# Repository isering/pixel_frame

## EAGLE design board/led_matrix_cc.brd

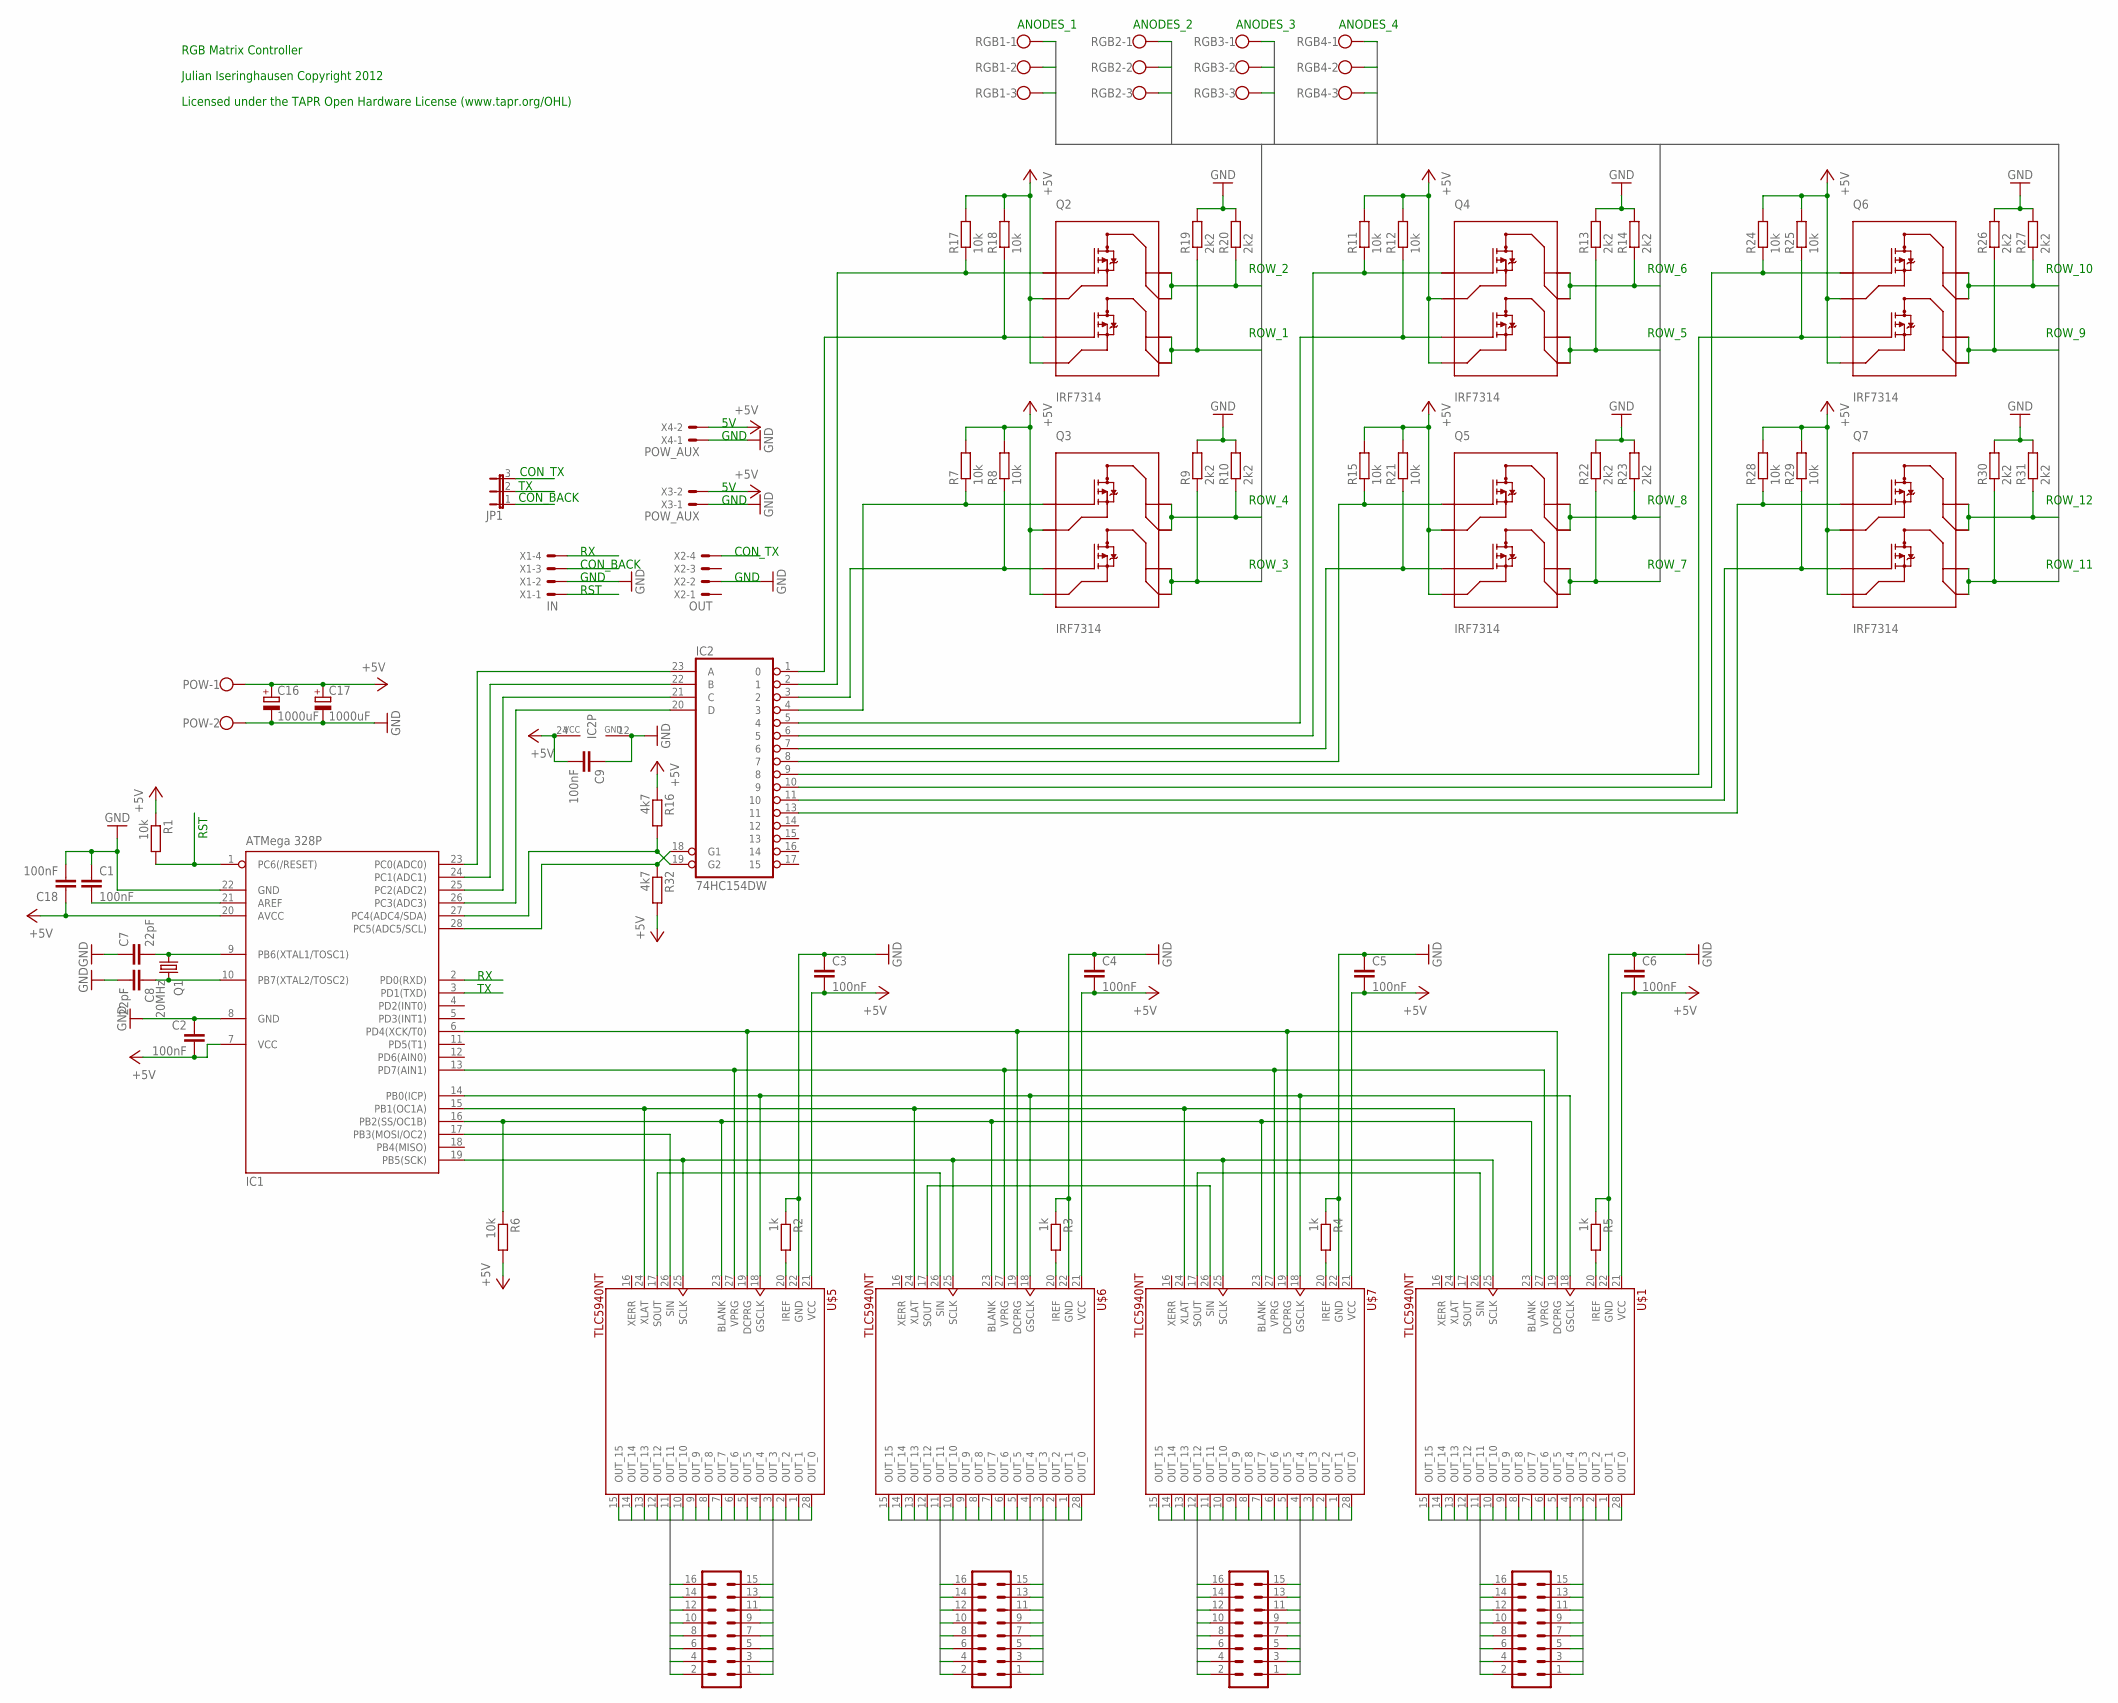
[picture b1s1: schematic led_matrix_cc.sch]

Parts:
C1, C2, C3, C4, C5, C6, C9, C18: 100nF; C1206
C7, C8: 22pF; C1206
C16, C17: 1000uF; E5-10,5
CON_TLC_1, CON_TLC_2, CON_TLC_3, CON_TLC_4: ML16
IC1: ATMega 328P; DIL28-3
IC2: 74HC154DW; SO24W
JP1: JP2E; JP2
POW: W237-102
Q1: 20MHz; HC49U70
Q2, Q3, Q4, Q5, Q6, Q7: IRF7314; TRANSISTOR-FET-MOD_SO08-IRF
R1, R6: 10k; R1206
R2, R3, R4, R5: 1k; R1206
R7, R8, R11, R12, R15, R17, R18, R21, R24, R25, R28, R29: 10k; RCL_R1206
R9, R10, R13, R14, R19, R20, R22, R23, R26, R27, R30, R31: 2k2; RCL_R1206
R16, R32: 4k7; R1206
RGB1, RGB2, RGB3, RGB4: W237-103
U$1, U$5, U$6, U$7: TLC5940NT; TLC5940_DIP-28
X1: IN; 22-23-2041
X2: OUT; 22-23-2041
X3, X4: POW_AUX; 22-23-2021

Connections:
+5V: C2.2, C3.2, C4.2, C5.2, C6.2, C9.2, C16.+, C17.+, C18.1, IC1.7 (VCC), IC1.20 (AVCC), IC2.24 (VCC), POW.1, Q2.1 (S1), Q2.3 (S2), Q3.1 (S1), Q3.3 (S2), Q4.1 (S1), Q4.3 (S2), Q5.1 (S1), Q5.3 (S2), Q6.1 (S1), Q6.3 (S2), Q7.1 (S1), Q7.3 (S2), R1.1, R6.2, R7.2, R8.2, R11.2, R12.2, R15.2, R16.1, R17.2, R18.2, R21.2, R24.2, R25.2, R28.2, R29.2, R32.2, U$1.21 (VCC), U$5.21 (VCC), U$6.21 (VCC), U$7.21 (VCC), X3.2, X4.2
CON_BACK: JP1.1, X1.3
CON_TX: JP1.3, X2.4
GND: C1.1, C2.1, C3.1, C4.1, C5.1, C6.1, C7.1, C8.2, C9.1, C16.-, C17.-, C18.2, IC1.8 (GND), IC1.22 (GND), IC2.12 (GND), POW.2, R2.1, R3.1, R4.1, R5.1, R9.2, R10.2, R13.2, R14.2, R19.2, R20.2, R22.2, R23.2, R26.2, R27.2, R30.2, R31.2, U$1.22 (GND), U$5.22 (GND), U$6.22 (GND), U$7.22 (GND), X1.2, X2.2, X3.1, X4.1
unnamed: IC2.6 (5), Q4.2 (G1), R11.1
unnamed: IC2.5 (4), Q4.4 (G2), R12.1
unnamed: IC1.17 (PB3(MOSI/OC2)), U$5.26 (SIN)
unnamed: U$5.17 (SOUT), U$6.26 (SIN)
unnamed: U$6.17 (SOUT), U$7.26 (SIN)
unnamed: IC1.19 (PB5(SCK)), U$1.25 (SCLK), U$5.25 (SCLK), U$6.25 (SCLK), U$7.25 (SCLK)
unnamed: IC1.16 (PB2(SS/OC1B)), R6.1, U$1.23 (BLANK), U$5.23 (BLANK), U$6.23 (BLANK), U$7.23 (BLANK)
unnamed: C7.2, IC1.9 (PB6(XTAL1/TOSC1)), Q1.1
unnamed: IC1.23 (PC0(ADC0)), IC2.23 (A)
unnamed: IC1.24 (PC1(ADC1)), IC2.22 (B)
unnamed: IC1.25 (PC2(ADC2)), IC2.21 (C)
unnamed: IC1.26 (PC3(ADC3)), IC2.20 (D)
unnamed: IC1.15 (PB1(OC1A)), U$1.24 (XLAT), U$5.24 (XLAT), U$6.24 (XLAT), U$7.24 (XLAT)
unnamed: IC1.6 (PD4(XCK/T0)), U$1.19 (DCPRG), U$5.19 (DCPRG), U$6.19 (DCPRG), U$7.19 (DCPRG)
unnamed: IC1.13 (PD7(AIN1)), U$1.27 (VPRG), U$5.27 (VPRG), U$6.27 (VPRG), U$7.27 (VPRG)
unnamed: IC1.14 (PB0(ICP)), U$1.18 (GSCLK), U$5.18 (GSCLK), U$6.18 (GSCLK), U$7.18 (GSCLK)
unnamed: U$1.26 (SIN), U$7.17 (SOUT)
unnamed: R4.2, U$7.20 (IREF)
unnamed: IC1.28 (PC5(ADC5/SCL)), IC2.18 (G1), R32.1
unnamed: IC2.9 (8), Q6.4 (G2), R25.1
unnamed: R5.2, U$1.20 (IREF)
unnamed: IC2.8 (7), Q5.2 (G1), R15.1
unnamed: IC2.10 (9), Q6.2 (G1), R24.1
unnamed: R3.2, U$6.20 (IREF)
unnamed: R2.2, U$5.20 (IREF)
unnamed: IC2.13 (11), Q7.2 (G1), R28.1
unnamed: C8.1, IC1.10 (PB7(XTAL2/TOSC2)), Q1.2
unnamed: IC2.1 (0), Q2.4 (G2), R18.1
unnamed: IC2.2 (1), Q2.2 (G1), R17.1
unnamed: IC2.4 (3), Q3.2 (G1), R7.1
unnamed: IC2.3 (2), Q3.4 (G2), R8.1
unnamed: IC2.11 (10), Q7.4 (G2), R29.1
unnamed: IC2.7 (6), Q5.4 (G2), R21.1
unnamed: C1.2, IC1.21 (AREF)
unnamed: IC1.27 (PC4(ADC4/SDA)), IC2.19 (G2), R16.2
ROW1: Q2.5 (D2B), Q2.6 (D2A), R19.1, RGB1.1
ROW2: Q2.7 (D1B), Q2.8 (D1A), R20.1, RGB1.2
ROW3: Q3.5 (D2B), Q3.6 (D2A), R9.1, RGB1.3
ROW4: Q3.7 (D1B), Q3.8 (D1A), R10.1, RGB2.1
ROW5: Q4.5 (D2B), Q4.6 (D2A), R13.1, RGB2.2
ROW6: Q4.7 (D1B), Q4.8 (D1A), R14.1, RGB2.3
ROW7: Q5.5 (D2B), Q5.6 (D2A), R22.1, RGB3.1
ROW8: Q5.7 (D1B), Q5.8 (D1A), R23.1, RGB3.2
ROW9: Q6.5 (D2B), Q6.6 (D2A), R26.1, RGB3.3
ROW10: Q6.7 (D1B), Q6.8 (D1A), R27.1, RGB4.1
ROW11: Q7.5 (D2B), Q7.6 (D2A), R30.1, RGB4.2
ROW12: Q7.7 (D1B), Q7.8 (D1A), R31.1, RGB4.3
RST: IC1.1 (PC6(/RESET)), R1.2, X1.1
RX: IC1.2 (PD0(RXD)), X1.4
T1_1: CON_TLC_1.1, U$5.28 (OUT_0)
T1_2: CON_TLC_1.2, U$5.1 (OUT_1)
T1_3: CON_TLC_1.3, U$5.2 (OUT_2)
T1_4: CON_TLC_1.4, U$5.3 (OUT_3)
T1_5: CON_TLC_1.5, U$5.4 (OUT_4)
T1_6: CON_TLC_1.6, U$5.5 (OUT_5)
T1_7: CON_TLC_1.7, U$5.6 (OUT_6)
T1_8: CON_TLC_1.8, U$5.7 (OUT_7)
T1_9: CON_TLC_1.9, U$5.8 (OUT_8)
T1_10: CON_TLC_1.10, U$5.9 (OUT_9)
T1_11: CON_TLC_1.11, U$5.10 (OUT_10)
T1_12: CON_TLC_1.12, U$5.11 (OUT_11)
T1_13: CON_TLC_1.13, U$5.12 (OUT_12)
T1_14: CON_TLC_1.14, U$5.13 (OUT_13)
T1_15: CON_TLC_1.15, U$5.14 (OUT_14)
T1_16: CON_TLC_1.16, U$5.15 (OUT_15)
T2_1: CON_TLC_2.1, U$6.28 (OUT_0)
T2_2: CON_TLC_2.2, U$6.1 (OUT_1)
T2_3: CON_TLC_2.3, U$6.2 (OUT_2)
T2_4: CON_TLC_2.4, U$6.3 (OUT_3)
T2_5: CON_TLC_2.5, U$6.4 (OUT_4)
T2_6: CON_TLC_2.6, U$6.5 (OUT_5)
T2_7: CON_TLC_2.7, U$6.6 (OUT_6)
T2_8: CON_TLC_2.8, U$6.7 (OUT_7)
T2_9: CON_TLC_2.9, U$6.8 (OUT_8)
T2_10: CON_TLC_2.10, U$6.9 (OUT_9)
T2_11: CON_TLC_2.11, U$6.10 (OUT_10)
T2_12: CON_TLC_2.12, U$6.11 (OUT_11)
T2_13: CON_TLC_2.13, U$6.12 (OUT_12)
T2_14: CON_TLC_2.14, U$6.13 (OUT_13)
T2_15: CON_TLC_2.15, U$6.14 (OUT_14)
T2_16: CON_TLC_2.16, U$6.15 (OUT_15)
T3_1: CON_TLC_3.1, U$7.28 (OUT_0)
T3_2: CON_TLC_3.2, U$7.1 (OUT_1)
T3_3: CON_TLC_3.3, U$7.2 (OUT_2)
T3_4: CON_TLC_3.4, U$7.3 (OUT_3)
T3_5: CON_TLC_3.5, U$7.4 (OUT_4)
T3_6: CON_TLC_3.6, U$7.5 (OUT_5)
T3_7: CON_TLC_3.7, U$7.6 (OUT_6)
T3_8: CON_TLC_3.8, U$7.7 (OUT_7)
T3_9: CON_TLC_3.9, U$7.8 (OUT_8)
T3_10: CON_TLC_3.10, U$7.9 (OUT_9)
T3_11: CON_TLC_3.11, U$7.10 (OUT_10)
T3_12: CON_TLC_3.12, U$7.11 (OUT_11)
T3_13: CON_TLC_3.13, U$7.12 (OUT_12)
T3_14: CON_TLC_3.14, U$7.13 (OUT_13)
T3_15: CON_TLC_3.15, U$7.14 (OUT_14)
T3_16: CON_TLC_3.16, U$7.15 (OUT_15)
T4_1: CON_TLC_4.1, U$1.28 (OUT_0)
T4_2: CON_TLC_4.2, U$1.1 (OUT_1)
T4_3: CON_TLC_4.3, U$1.2 (OUT_2)
T4_4: CON_TLC_4.4, U$1.3 (OUT_3)
T4_5: CON_TLC_4.5, U$1.4 (OUT_4)
T4_6: CON_TLC_4.6, U$1.5 (OUT_5)
T4_7: CON_TLC_4.7, U$1.6 (OUT_6)
T4_8: CON_TLC_4.8, U$1.7 (OUT_7)
T4_9: CON_TLC_4.9, U$1.8 (OUT_8)
T4_10: CON_TLC_4.10, U$1.9 (OUT_9)
T4_11: CON_TLC_4.11, U$1.10 (OUT_10)
T4_12: CON_TLC_4.12, U$1.11 (OUT_11)
T4_13: CON_TLC_4.13, U$1.12 (OUT_12)
T4_14: CON_TLC_4.14, U$1.13 (OUT_13)
T4_15: CON_TLC_4.15, U$1.14 (OUT_14)
T4_16: CON_TLC_4.16, U$1.15 (OUT_15)
TX: IC1.3 (PD1(TXD)), JP1.2

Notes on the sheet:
ROW_1
ROW_2
ROW_3
ROW_4
ROW_5
ROW_6
ROW_7
ROW_8
ROW_9
ROW_10
ROW_11
ROW_12
ANODES_1
ANODES_2
ANODES_3
ANODES_4
RST
GND
CON_BACK
CON_TX
Licensed under the TAPR Open Hardware License (www.tapr.org/OHL)
RGB Matrix Controller
Julian Iseringhausen Copyright 2012

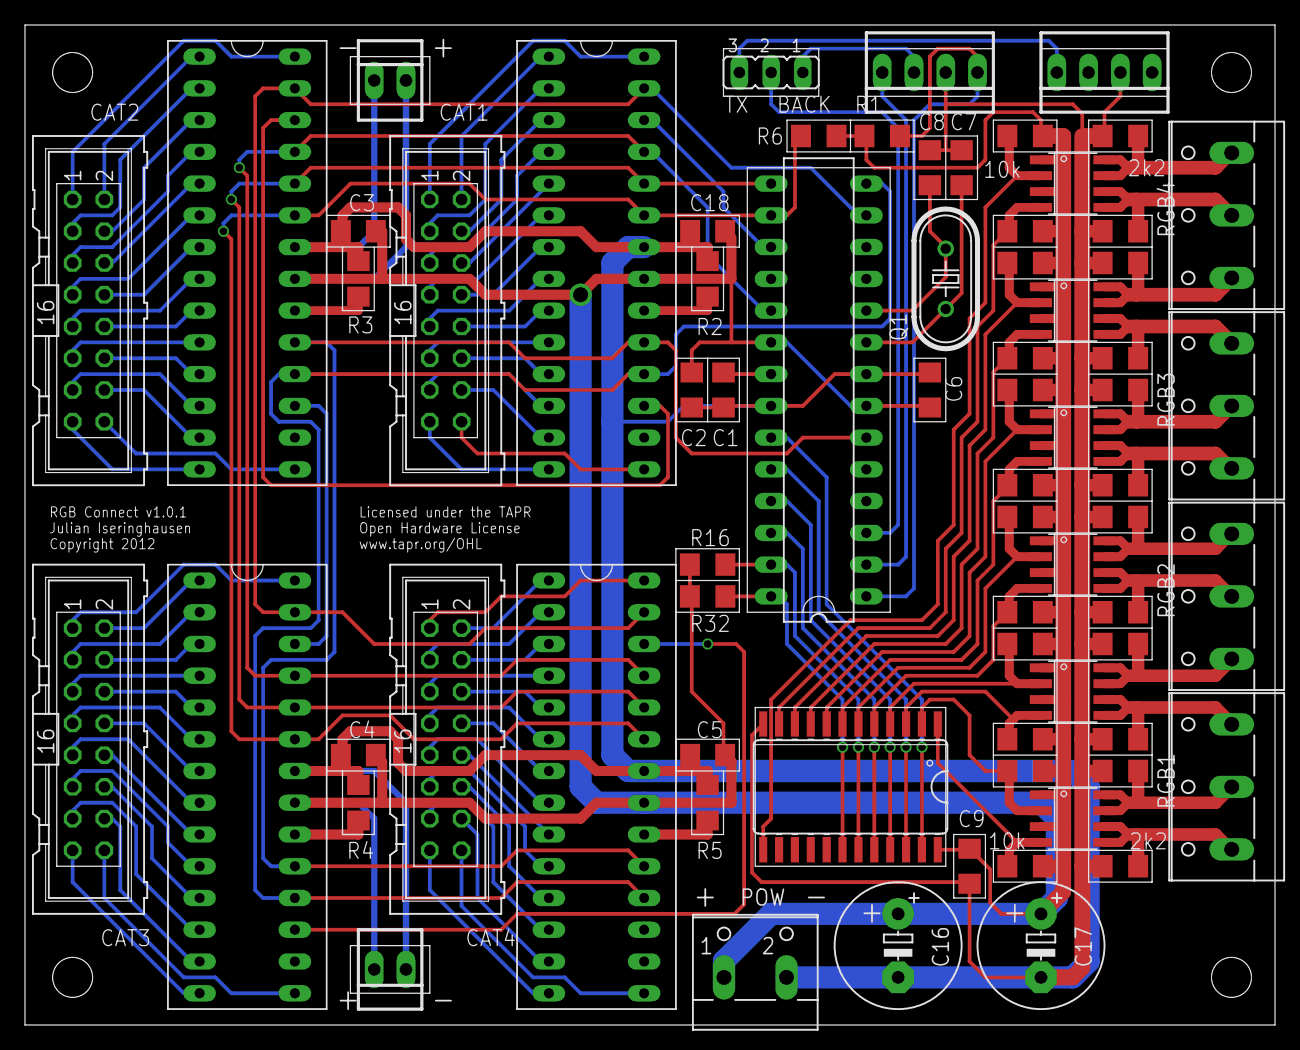
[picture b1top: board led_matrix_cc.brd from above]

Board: 2 copper layers, 100.0 x 80.0 mm, 71 parts (0 on the bottom side), 118 nets.

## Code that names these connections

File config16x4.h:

/*
 * config.h
 *
 * Created: 12.10.2012 01:39:39
 *  Author: Julian Iseringhausen
 */ 


#ifndef CONFIG_H_
#define CONFIG_H_

#ifndef F_CPU
#define F_CPU 20000000UL
#endif

#define TLC5940_N 1
#define TLC5940_MULTIPLEX_N 12

#define SIZE_X 16              // Number of LEDs in x direction
#define SIZE_Y 4               // Number of LEDs in y direction
#define SIZE_X_BITS 4          // Number of bits necessary to represent SIZE_X - 1
#define SIZE_Y_BITS 2          // Number of bits nevessary to represent SIZE_Y - 1
´
/* Pins for multiplexing */
#define MULTIPLEX_DDR DDRC 
#define MULTIPLEX_PORT PORTC
#define MULTIPLEX_MASK 0x3f

/* DCPRG pin */
#define DCPRG_DDR DDRD
#define DCPRG_PORT PORTD
#define DCPRG_PIN PD4

/* VPRG pin */
#define VPRG_DDR DDRD
#define VPRG_PORT PORTD
#define VPRG_PIN PD7

/* XLAT pin */
#define XLAT_DDR DDRB
#define XLAT_PORT PORTB
#define XLAT_PIN PB1

/* SIN pin */
#define SIN_DDR DDRB
#define SIN_PORT PORTB
#define SIN_PIN PB3

/* SCLK pin */
#define SCLK_DDR DDRB
#define SCLK_PORT PORTB
#define SCLK_PIN PB5

/* BLANK pin */
#define BLANK_DDR DDRB
#define BLANK_PORT PORTB
#define BLANK_PIN PB2

/* GPIO register flags */
#define FLAGS GPIOR0
#define FLAG_GS_UPDATE 0
#define FLAG_XLAT_NEEDS_PULSE 1
#define FLAG_FPS_UPDATE 2
#define FLAG_EFFECT_MODE_CHANGED 3
#define FLAG_UART_BIT_9 4

#define AVRSNIPPETS_USE_RANDOM
#define AVRSNIPPETS_USE_RINGBUFFER
#define AVRSNIPPETS_USE_SEED_EEPROM
#define AVRSNIPPETS_USE_SERIAL

#define SERIAL_ENABLE_RX
#define SERIAL_ENABLE_RX_INT
#define SERIAL_BAUDRATE 250000UL
#define SERIAL_CHARSIZE 9

/* For convenience */
#define EFFECT_GS_UPDATE 0
#define EFFECT_GS_NOUPDATE 1

/* EEPROM range for random number seed */
#define RANDOM_EEPROM_BEGIN 0
#define RANDOM_EEPROM_END 256

/* EEPROM range for settings */
#define SETTINGS_EEPROM_BEGIN 256
#define SETTINGS_EEPROM_END 512

#ifdef __ASSEMBLER__

#define tmp  r18
#define tmp2  r19
#define tmp3  r20

#endif


#endif /* CONFIG_H_ */

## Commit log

2013-09-26 Initial commit.
2013-09-26 Add board schematics.
2013-09-26 Adjustments for 16x4 frame.
